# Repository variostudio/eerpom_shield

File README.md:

This is a shield for Arduino Mega Pro board to interact with SST39 eeprom chip

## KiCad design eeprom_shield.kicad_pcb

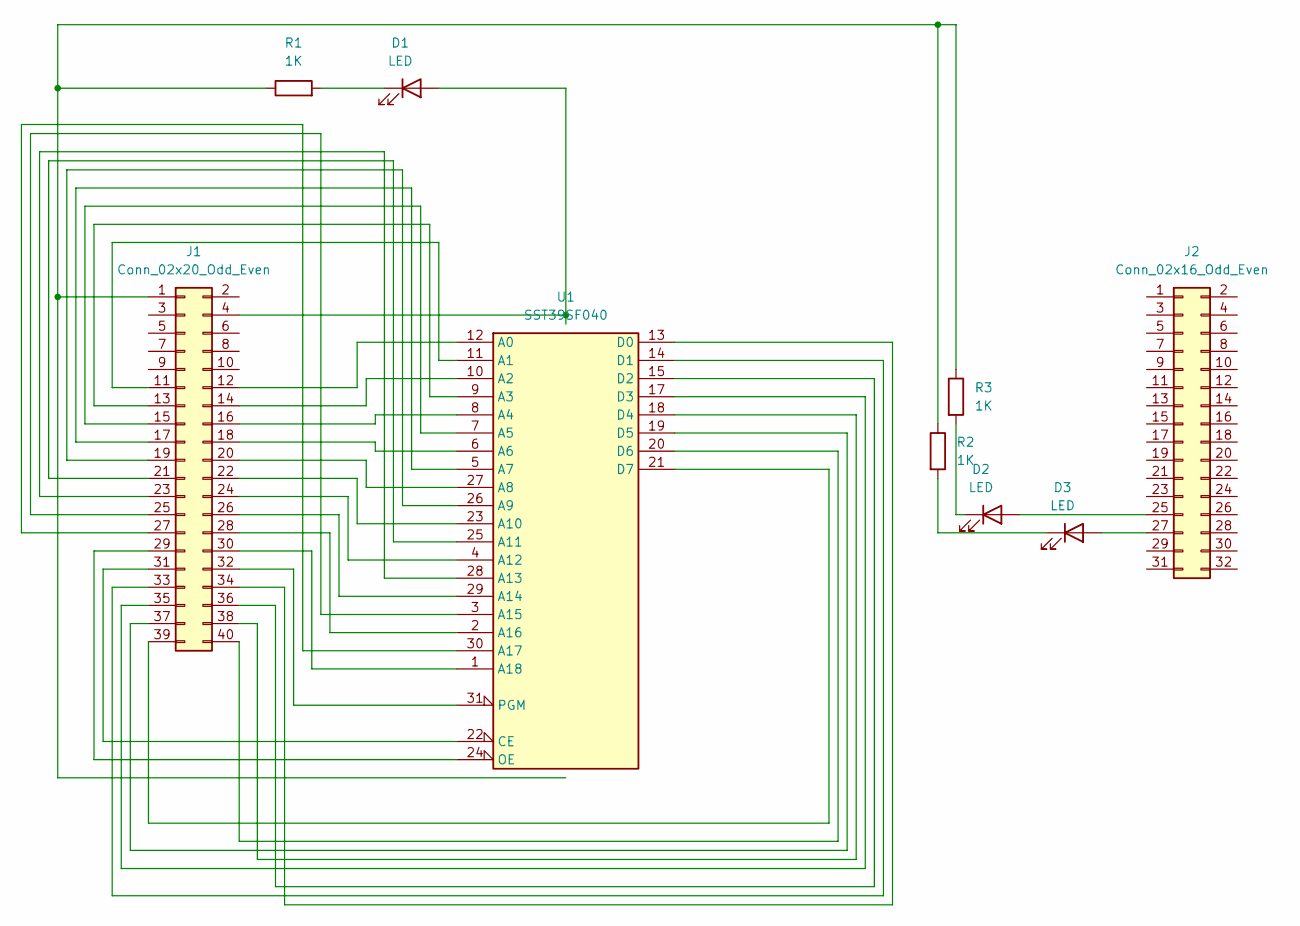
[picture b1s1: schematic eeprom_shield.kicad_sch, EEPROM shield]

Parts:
D1, D2, D3: LED; LED_D3.0mm
J1: Conn_02x20_Odd_Even; PinHeader_2x20_P2.54mm_Vertical
J2: Conn_02x16_Odd_Even; PinHeader_2x16_P2.54mm_Vertical
R1, R2, R3: 1K; R_Axial_DIN0207_L6.3mm_D2.5mm_P10.16mm_Horizontal
U1: SST39SF040; DIP-32_W15.24mm_Socket

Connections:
GND: J1.1, R1.1, R2.1, R3.1, U1.16 (GND)
unnamed: D1.1 (K), R1.2
unnamed: D2.1 (K), R3.2
unnamed: D2.2 (A), J2.25
unnamed: D3.1 (K), R2.2
unnamed: D3.2 (A), J2.27
unnamed: J1.11, U1.11 (A1)
unnamed: J1.12, U1.12 (A0)
unnamed: J1.13, U1.9 (A3)
unnamed: J1.14, U1.10 (A2)
unnamed: J1.15, U1.7 (A5)
unnamed: J1.16, U1.8 (A4)
unnamed: J1.17, U1.5 (A7)
unnamed: J1.18, U1.6 (A6)
unnamed: J1.19, U1.26 (A9)
unnamed: J1.20, U1.27 (A8)
unnamed: J1.21, U1.25 (A11)
unnamed: J1.22, U1.23 (A10)
unnamed: J1.23, U1.28 (A13)
unnamed: J1.24, U1.4 (A12)
unnamed: J1.25, U1.3 (A15)
unnamed: J1.26, U1.29 (A14)
unnamed: J1.27, U1.30 (A17)
unnamed: J1.28, U1.2 (A16)
unnamed: J1.29, U1.24 (OE)
unnamed: J1.30, U1.1 (A18)
unnamed: J1.31, U1.22 (CE)
unnamed: J1.32, U1.31 (PGM)
unnamed: J1.33, U1.14 (D1)
unnamed: J1.34, U1.13 (D0)
unnamed: J1.35, U1.17 (D3)
unnamed: J1.36, U1.15 (D2)
unnamed: J1.37, U1.19 (D5)
unnamed: J1.38, U1.18 (D4)
unnamed: J1.39, U1.21 (D7)
unnamed: J1.40, U1.20 (D6)
VCC: D1.2 (A), J1.4, U1.32 (VCC)

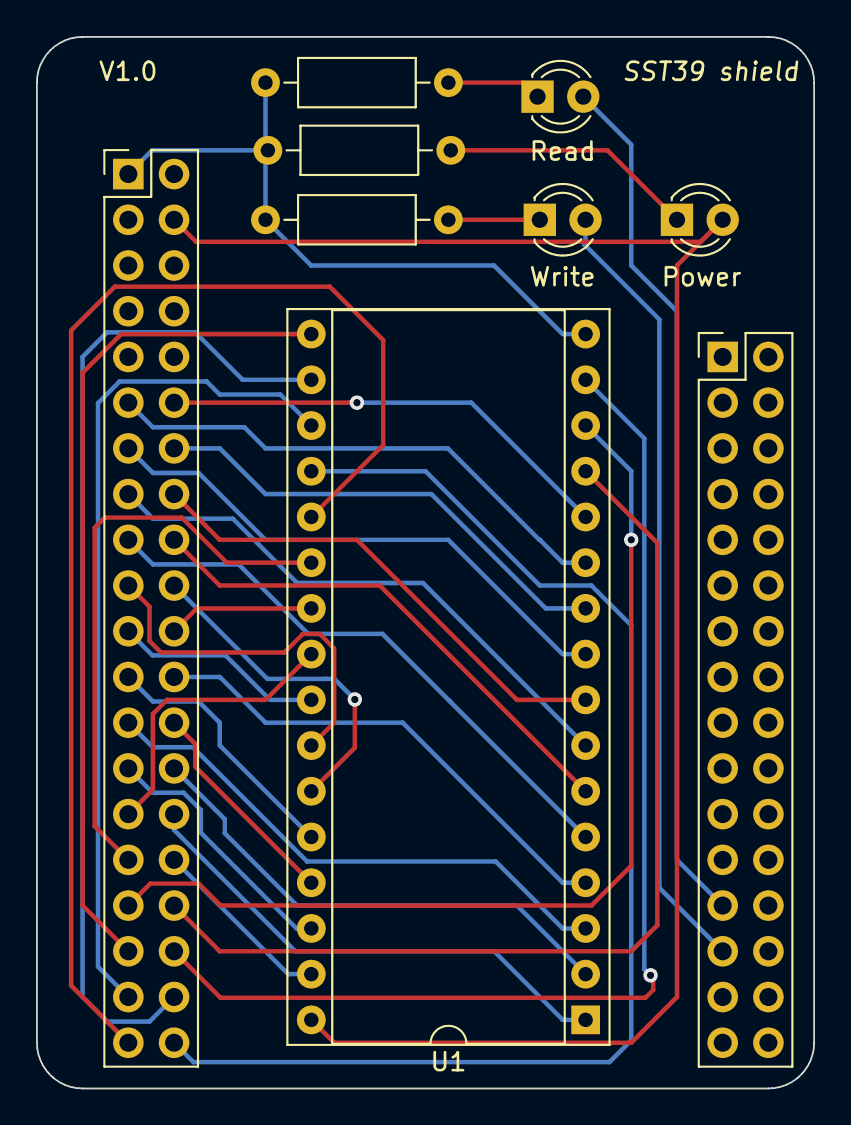
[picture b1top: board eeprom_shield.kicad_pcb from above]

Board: 2 copper layers, 43.2 x 58.4 mm, 9 parts (0 on the bottom side), 37 nets.

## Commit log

2022-11-07 Create eeprom_shield.zip
    Shield v1.0 added
2022-11-07 Create eeprom_shield.svg
    SVG added
2022-11-07 Create eeprom_tool_mega.ino
    Arduino code example added
2022-11-24 Version 1.1
2022-11-24 Create arduino_mega_pro.jpg
    Arduino Mega Pro pinout added
2022-11-24 Comments added
2022-11-25 Full address range support
